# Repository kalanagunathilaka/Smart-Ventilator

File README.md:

# Smart Ventilator

This project aims to develop a low cost smart ventilator system that requires minimum professional interaction to operate using Atmega32 Microcontroller

**Objectives**

- To detect patient’s blood oxygen levels using the blood oxygen sensor (MAX30102)  and to provide oxygen where necessary.
- To monitor the patient’s vitals using the temperature sensor, pressure sensor, heart rate sensor and LCD display and send an alert message to a medical personnel using the gsm module or sound the speaker when it is necessary.
- To monitor a patient's blood oxygen level and automatically switch off oxygen supply when not needed.
- To be able to manually control all parameters of the air and oxygen flow supplied to the patient.

**System Block Diagram**

**Schematic of the product**

**3D Design of the System**

**PCB & 3D View of the Main Board**

**PCB & 3D View of the Heart Rate & SPO2**

**PCB & 3D View of Body Temperature Sensor**

**PCB & 3D View of Power Supply**

[**3D Animation**](https://dms.uom.lk/s/HgEqCMnCMRMiKYt)

**Software Used**

- Microchip Studio - Program Microcontroller
- Proteus Design Suite - Design Schematic Diagram
- KiCad EDA - Design PCB
- Blender - Design 3D View
- Adobe After Effects & Premiere Pro - Design 3D Animation

**Contributors**

- [Yesitha Sathsara](https://github.com/yesitha)
- [Shakila Kularathna](https://github.com/shakila2030)
- [Nelaka Gunawardhana](https://github.com/NelakaGunawardhana)
- [Kalana Gunathilaka](https://github.com/KalanaLakshan)
- [Piyumanthi Nisansala](https://github.com/Piyumanthi)

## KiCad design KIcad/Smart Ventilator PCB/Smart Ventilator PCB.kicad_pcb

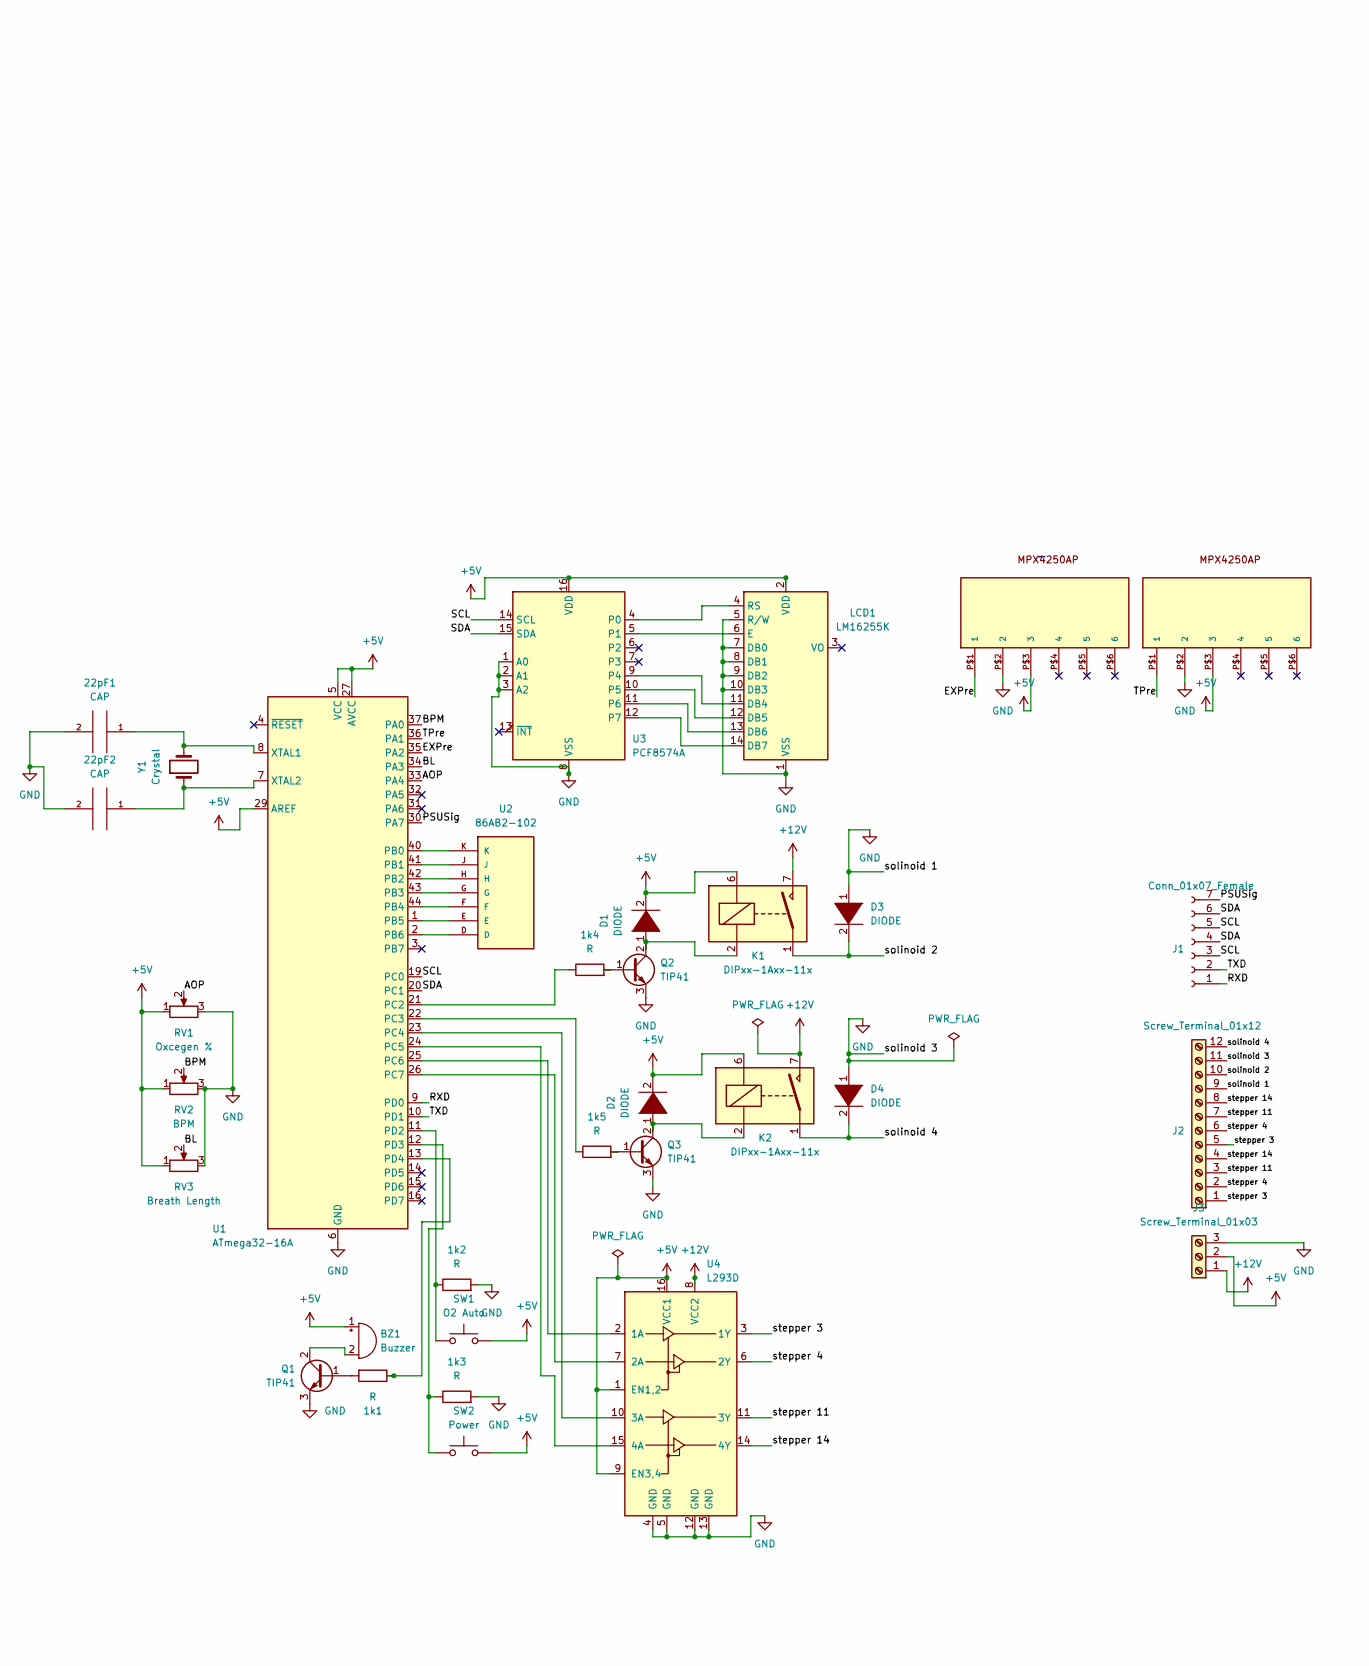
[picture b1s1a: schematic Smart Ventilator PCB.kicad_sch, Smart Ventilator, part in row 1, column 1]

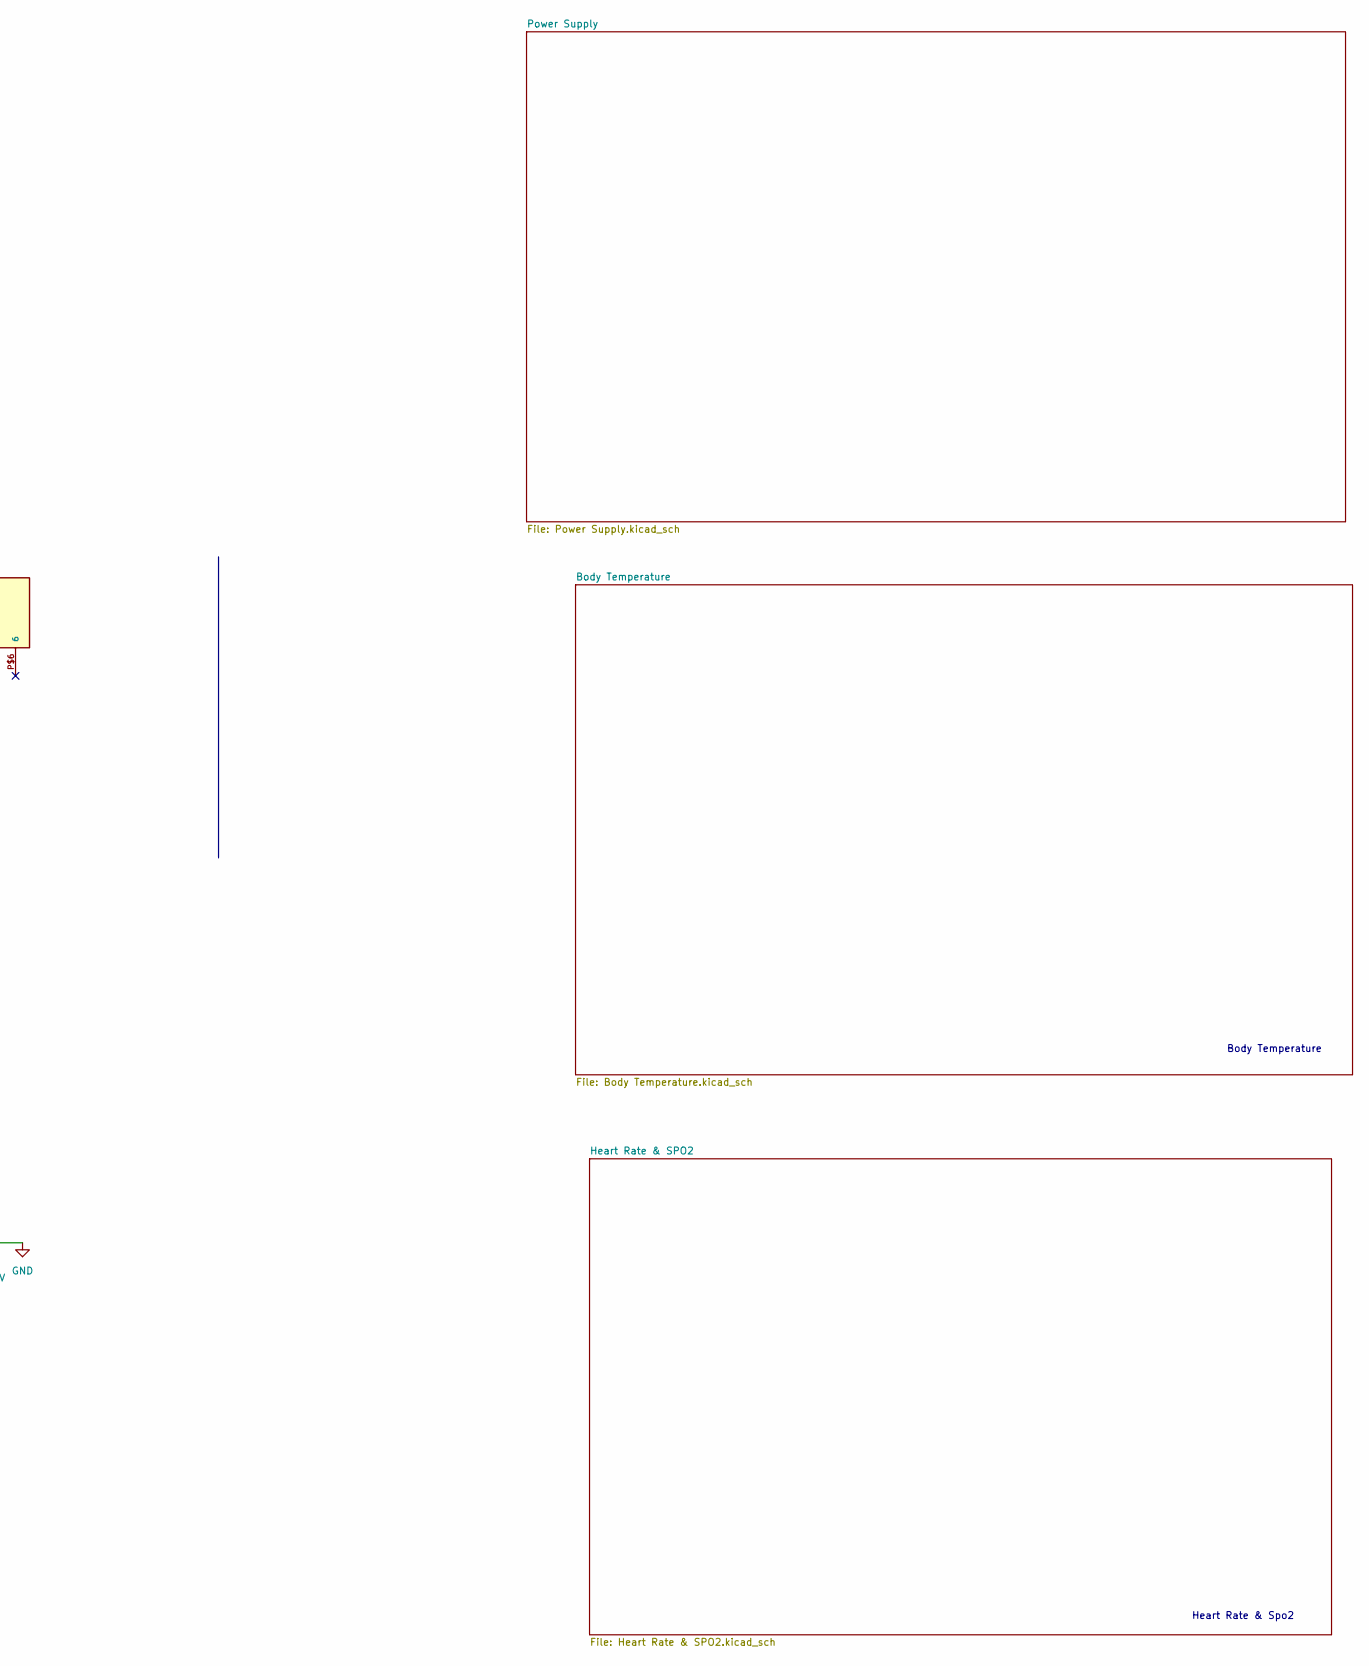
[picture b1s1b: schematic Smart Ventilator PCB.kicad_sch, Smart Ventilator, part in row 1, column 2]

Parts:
1k1, 1k2, 1k3, 1k4, 1k5: R; R_Axial_DIN0207_L6.3mm_D2.5mm_P10.16mm_Horizontal
22pF1, 22pF2: CAP; CP_Elec_3x5.3
BZ1: Buzzer; Buzzer_15x7.5RM7.6
D1, D2, D3, D4: DIODE; D_0201_0603Metric
J1: Conn_01x07_Female; PinHeader_1x07_P1.00mm_Vertical
J2: Screw_Terminal_01x12; TerminalBlock_4Ucon_1x12_P3.50mm_Horizontal
J3: Screw_Terminal_01x03; TerminalBlock_4Ucon_1x03_P3.50mm_Horizontal
K1, K2: DIPxx-1Axx-11x; Relay_StandexMeder_DIP_LowProfile
LCD1: LM16255K; LM16255
Q1, Q2, Q3: TIP41; TO-220-3_Vertical
RV1: Oxcegen %; Potentiometer_Bourns_3269W_Vertical
RV2: BPM; Potentiometer_Bourns_3269W_Vertical
RV3: Breath Length; Potentiometer_Bourns_3269W_Vertical
SW1: O2 Auto; SW_Push_1P1T_NO_6x6mm_H9.5mm
SW2: Power; SW_Push_1P1T_NO_6x6mm_H9.5mm
U1: ATmega32-16A; TQFP-44_10x10mm_P0.8mm
U2: 86AB2-102; KEYPAD_86AB2-102
U3: PCF8574A; DIL16
U4: L293D; DIP-16_W7.62mm
U5, U6: MPX4250AP
Y1: Crystal; Crystal_AT310_D3.0mm_L10.0mm_Horizontal

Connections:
+5V: BZ1.1 (-), D1.2 (A), D2.2 (A), J3.2, K1.6, K2.6, LCD1.2 (VDD), RV1.1, RV2.1, RV3.1, SW1.2, SW2.2, U1.5 (VCC), U1.17 (VCC), U1.27 (AVCC), U1.29 (AREF), U1.38 (VCC), U3.16 (VDD), U4.1 (EN1,2), U4.9 (EN3,4), U4.16 (VCC1), U5.P$3 (3), U6.P$3 (3)
+12V: J3.1, K1.7, K1.8, K2.7, K2.8, U4.8 (VCC2)
/AOP: RV1.2, U1.33 (PA4)
/BL: RV3.2, U1.34 (PA3)
/BPM: RV2.2, U1.37 (PA0)
/EXPre: U1.35 (PA2), U5.P$1 (1)
/PSUSig: J1.7, U1.30 (PA7)
/RXD: J1.1, U1.9 (PD0)
/SCL: J1.3, J1.5, U1.19 (PC0), U3.14 (SCL)
/SDA: J1.4, J1.6, U1.20 (PC1), U3.15 (SDA)
/TPre: U1.36 (PA1), U6.P$1 (1)
/TXD: J1.2, U1.10 (PD1)
/solinoid 2: D3.2 (A), J2.10, K1.1, K1.14
/solinoid 4: D4.2 (A), J2.12, K2.1, K2.14
/stepper 3: J2.1, J2.5, U4.3 (1Y)
/stepper 4: J2.2, J2.6, U4.6 (2Y)
/stepper 11: J2.3, J2.7, U4.11 (3Y)
/stepper 14: J2.4, J2.8, U4.14 (4Y)
GND: 1k2.2, 1k3.2, 22pF1.2, 22pF2.2, D3.1 (K), D4.1 (K), J2.9, J2.11, J3.3, K2.9, K2.13, LCD1.1 (VSS), LCD1.5 (R/W), LCD1.7 (DB0), LCD1.8 (DB1), LCD1.9 (DB2), LCD1.10 (DB3), Q1.3 (E), Q2.3 (E), Q3.3 (E), RV1.3, RV2.3, RV3.3, U1.6 (GND), U1.18 (GND), U1.28 (GND), U1.39 (GND), U3.1 (A0), U3.2 (A1), U3.3 (A2), U3.8 (VSS), U4.4 (GND), U4.5 (GND), U4.12 (GND), U4.13 (GND), U5.P$2 (2), U6.P$2 (2)
unnamed: 1k1.1, U1.13 (PD4)
unnamed: 1k1.2, Q1.1 (B)
unnamed: 1k2.1, SW1.1, U1.11 (PD2)
unnamed: 1k3.1, SW2.1, U1.12 (PD3)
unnamed: 1k4.1, U1.21 (PC2)
unnamed: 1k4.2, Q2.1 (B)
unnamed: 1k5.1, U1.22 (PC3)
unnamed: 1k5.2, Q3.1 (B)
unnamed: 22pF1.1, U1.8 (XTAL1), Y1.2
unnamed: 22pF2.1, U1.7 (XTAL2), Y1.1
unnamed: BZ1.2 (+), Q1.2 (C)
unnamed: D1.1 (K), K1.2, Q2.2 (C)
unnamed: D2.1 (K), K2.2, Q3.2 (C)
unnamed: LCD1.4 (RS), U3.4 (P0)
unnamed: LCD1.6 (E), U3.5 (P1)
unnamed: LCD1.11 (DB4), U3.9 (P4)
unnamed: LCD1.12 (DB5), U3.10 (P5)
unnamed: LCD1.13 (DB6), U3.11 (P6)
unnamed: LCD1.14 (DB7), U3.12 (P7)
unnamed: U1.1 (PB5), U2.E
unnamed: U1.2 (PB6), U2.D
unnamed: U1.23 (PC4), U4.10 (3A)
unnamed: U1.24 (PC5), U4.15 (4A)
unnamed: U1.25 (PC6), U4.2 (1A)
unnamed: U1.26 (PC7), U4.7 (2A)
unnamed: U1.40 (PB0), U2.K
unnamed: U1.41 (PB1), U2.J
unnamed: U1.42 (PB2), U2.H
unnamed: U1.43 (PB3), U2.G
unnamed: U1.44 (PB4), U2.F

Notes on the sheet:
Body Temperature
Heart Rate & Spo2

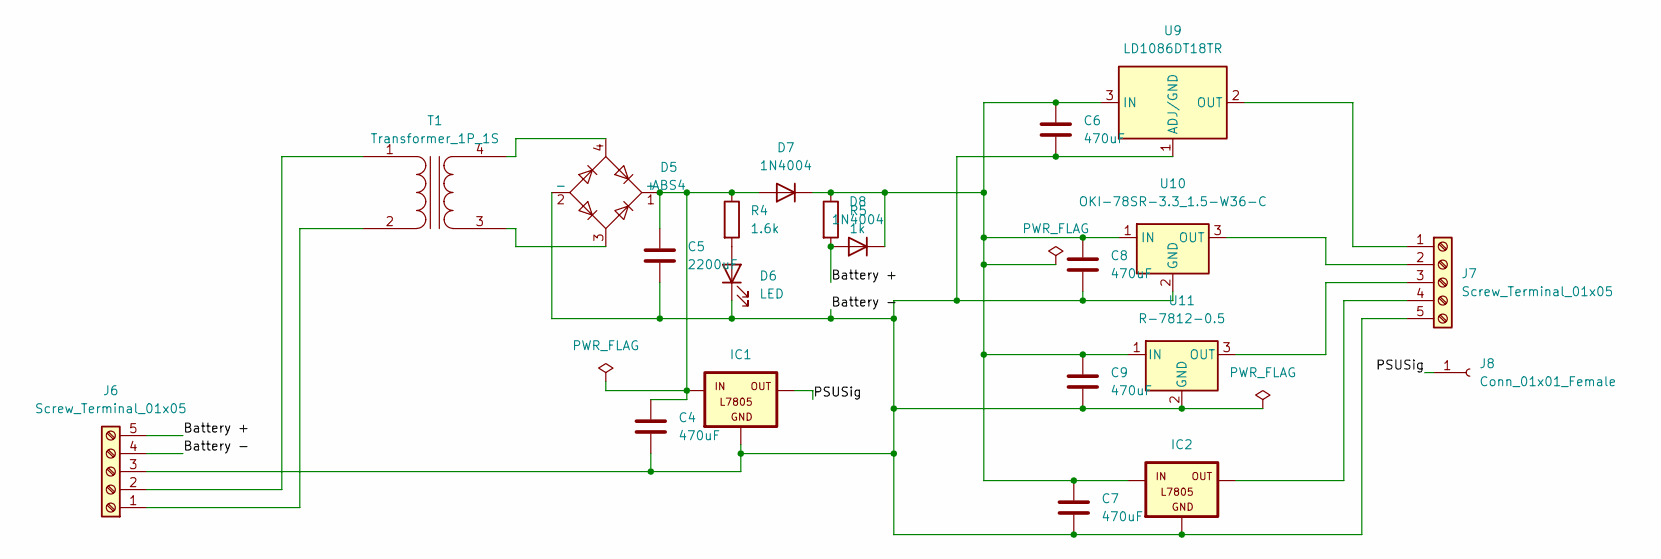
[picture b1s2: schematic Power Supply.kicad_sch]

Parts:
C4, C6, C7, C8, C9: 470uF; C_Elec_3x5.4
C5: 2200uF; C_Elec_5x5.4
D5: ABS4; Diode_Bridge_Diotec_ABS
D6: LED; LED_0603_1608Metric_Pad1.05x0.95mm_HandSolder
D7, D8: 1N4004; D_DO-41_SOD81_P10.16mm_Horizontal
IC1, IC2: L7805; 78XXL
J6, J7: Screw_Terminal_01x05; TerminalBlock_4Ucon_1x05_P3.50mm_Horizontal
J8: Conn_01x01_Female; PinHeader_1x01_P1.00mm_Vertical
R4: 1.6k; R_Axial_DIN0207_L6.3mm_D2.5mm_P10.16mm_Horizontal
R5: 1k; R_Axial_DIN0207_L6.3mm_D2.5mm_P10.16mm_Horizontal
T1: Transformer_1P_1S; Transformer_Toroid_Horizontal_D9.0mm_Amidon-T30
U9: LD1086DT18TR; TO-252-2
U10: OKI-78SR-3.3_1.5-W36-C; Converter_DCDC_Murata_OKI-78SR_Vertical
U11: R-7812-0.5; Converter_DCDC_RECOM_R-78E-0.5_THT

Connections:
/Power Supply/Battery +: D8.2 (A), J6.5, R5.2
/Power Supply/Battery -: C4.2, C5.2, C6.2, C7.2, C8.2, C9.2, D5.2 (-), D6.1 (K), IC1.GND, IC2.GND, J6.3, J6.4, J7.5, U9.1 (ADJ/GND), U10.2 (GND), U11.2 (GND)
/Power Supply/PSUSig: IC1.OUT, J8.1
unnamed: C4.1, C5.1, D5.1 (+), D7.2 (A), IC1.IN, R4.1
unnamed: C6.1, C7.1, C8.1, C9.1, D7.1 (K), D8.1 (K), IC2.IN, R5.1, U9.3 (IN), U10.1 (IN), U11.1 (IN)
unnamed: D5.3, T1.3 (SA)
unnamed: D5.4, T1.4 (SB)
unnamed: D6.2 (A), R4.2
unnamed: IC2.OUT, J7.4
unnamed: J6.1, T1.2 (AB)
unnamed: J6.2, T1.1 (AA)
unnamed: J7.1, U9.2 (OUT)
unnamed: J7.2, U10.3 (OUT)
unnamed: J7.3, U11.3 (OUT)

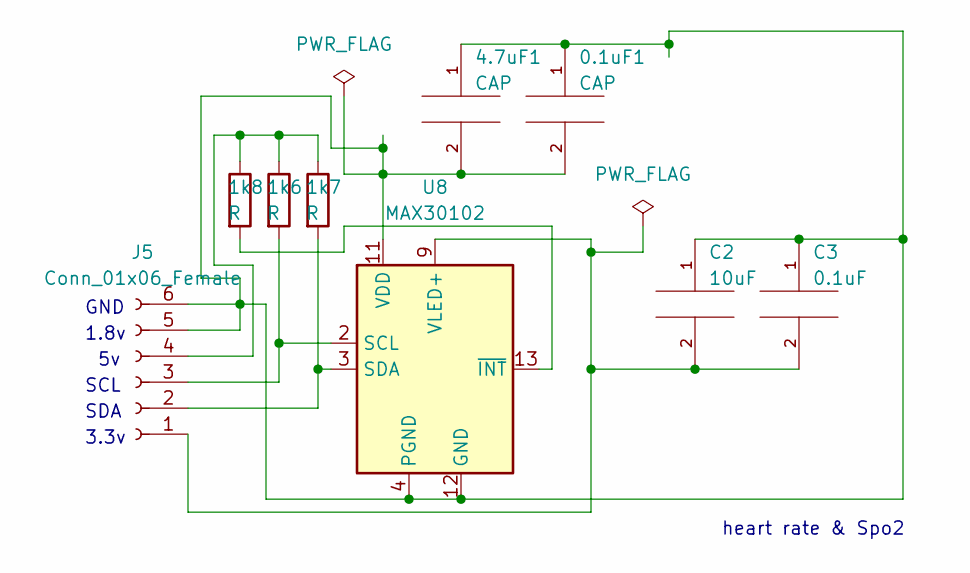
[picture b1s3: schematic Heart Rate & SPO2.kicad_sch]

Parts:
0.1uF1, 4.7uF1: CAP; CP_Elec_3x5.3
1k6, 1k7, 1k8: R; R_Axial_DIN0207_L6.3mm_D2.5mm_P10.16mm_Horizontal
C2: 10uF; CP_Elec_3x5.3
C3: 0.1uF; CP_Elec_3x5.3
J5: Conn_01x06_Female; PinHeader_1x06_P1.00mm_Vertical
U8: MAX30102; Maxim_OLGA-14_3.3x5.6mm_P0.8mm

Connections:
unnamed: 0.1uF1.1, 0.1uF1.2, 4.7uF1.1, 4.7uF1.2, C2.1, C3.1, J5.5, J5.6, U8.4 (PGND), U8.11 (VDD), U8.12 (GND)
unnamed: 1k6.1, 1k7.1, 1k8.1, J5.4
unnamed: 1k6.2, U8.13 (~INT)
unnamed: 1k7.2, J5.3, U8.2 (SCL)
unnamed: 1k8.2, J5.2, U8.3 (SDA)
unnamed: C2.2, C3.2, J5.1, U8.9 (VLED+), U8.10 (VLED+)

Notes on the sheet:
heart rate & Spo2
GND
SDA
1.8v
SCL
3.3v

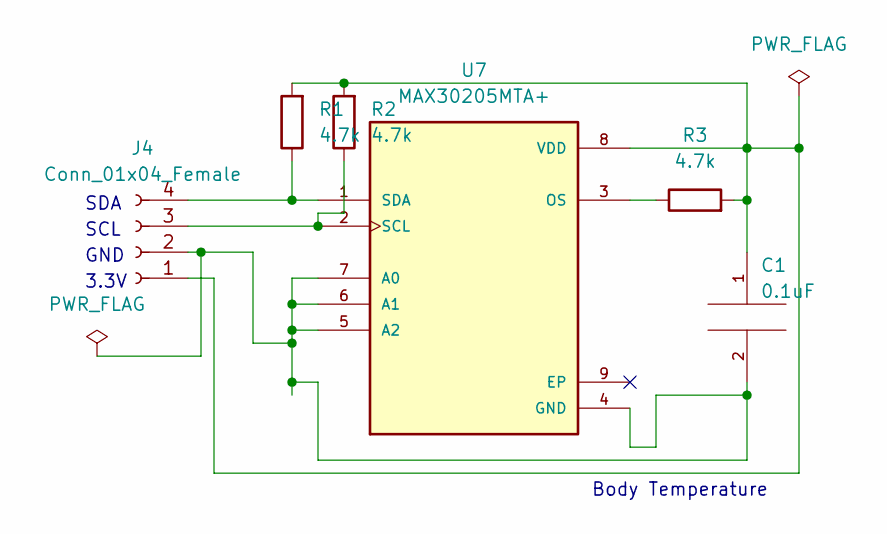
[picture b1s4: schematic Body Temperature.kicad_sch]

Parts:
C1: 0.1uF; CP_Elec_3x5.3
J4: Conn_01x04_Female; PinHeader_1x04_P1.00mm_Vertical
R1, R2, R3: 4.7k; R_Axial_DIN0207_L6.3mm_D2.5mm_P10.16mm_Horizontal
U7: MAX30205MTA+; SON65P300X300X80-9N

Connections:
unnamed: C1.1, J4.1, R1.2, R2.2, R3.2, U7.8 (VDD)
unnamed: C1.2, J4.2, U7.4 (GND), U7.5 (A2), U7.6 (A1), U7.7 (A0)
unnamed: J4.3, R2.1, U7.2 (SCL)
unnamed: J4.4, R1.1, U7.1 (SDA)
unnamed: R3.1, U7.3 (OS)

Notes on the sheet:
3.3V
SDA
SCL
Body Temperature
GND

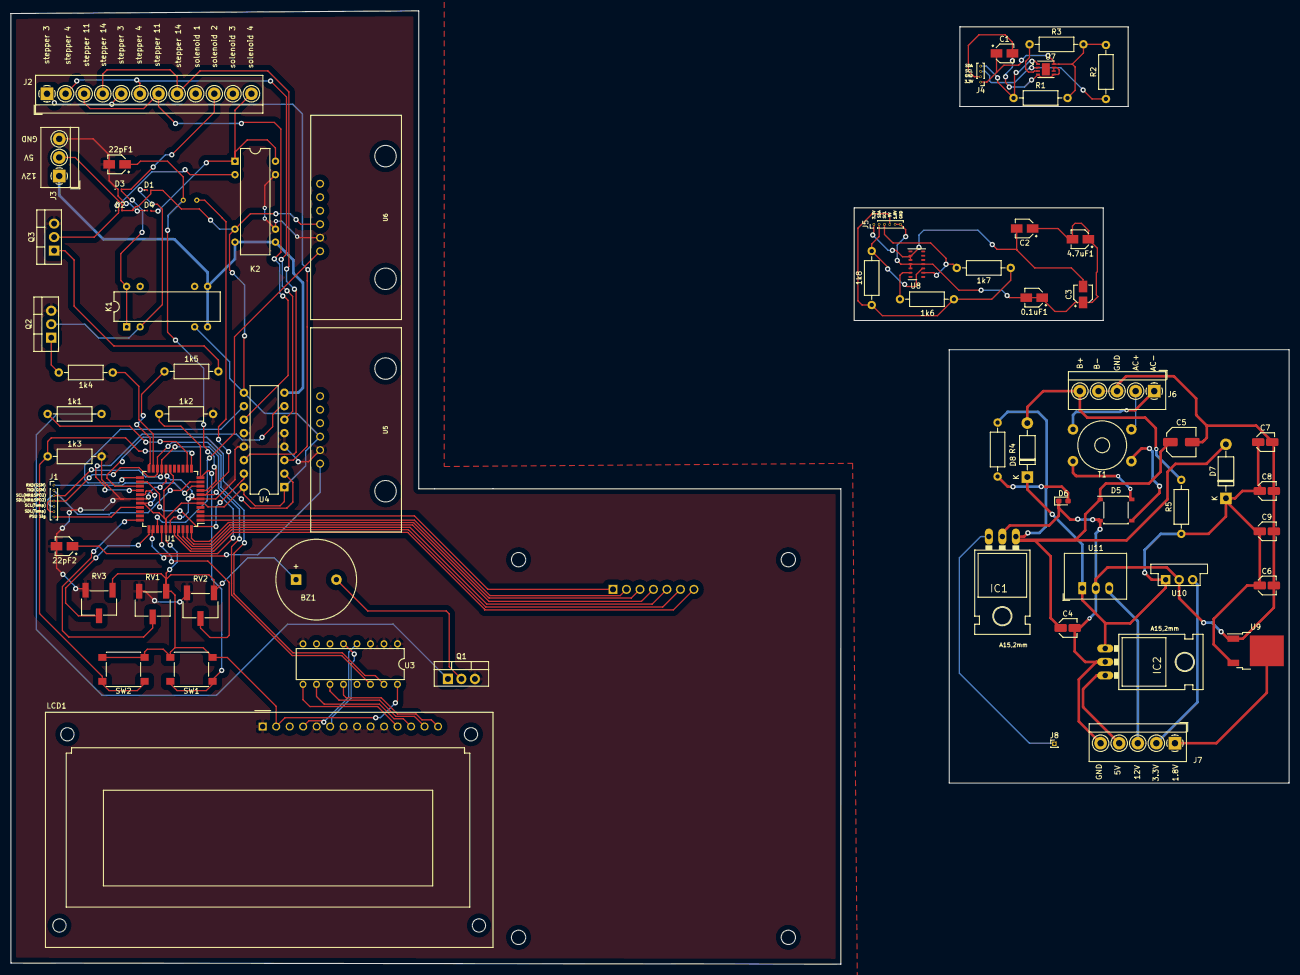
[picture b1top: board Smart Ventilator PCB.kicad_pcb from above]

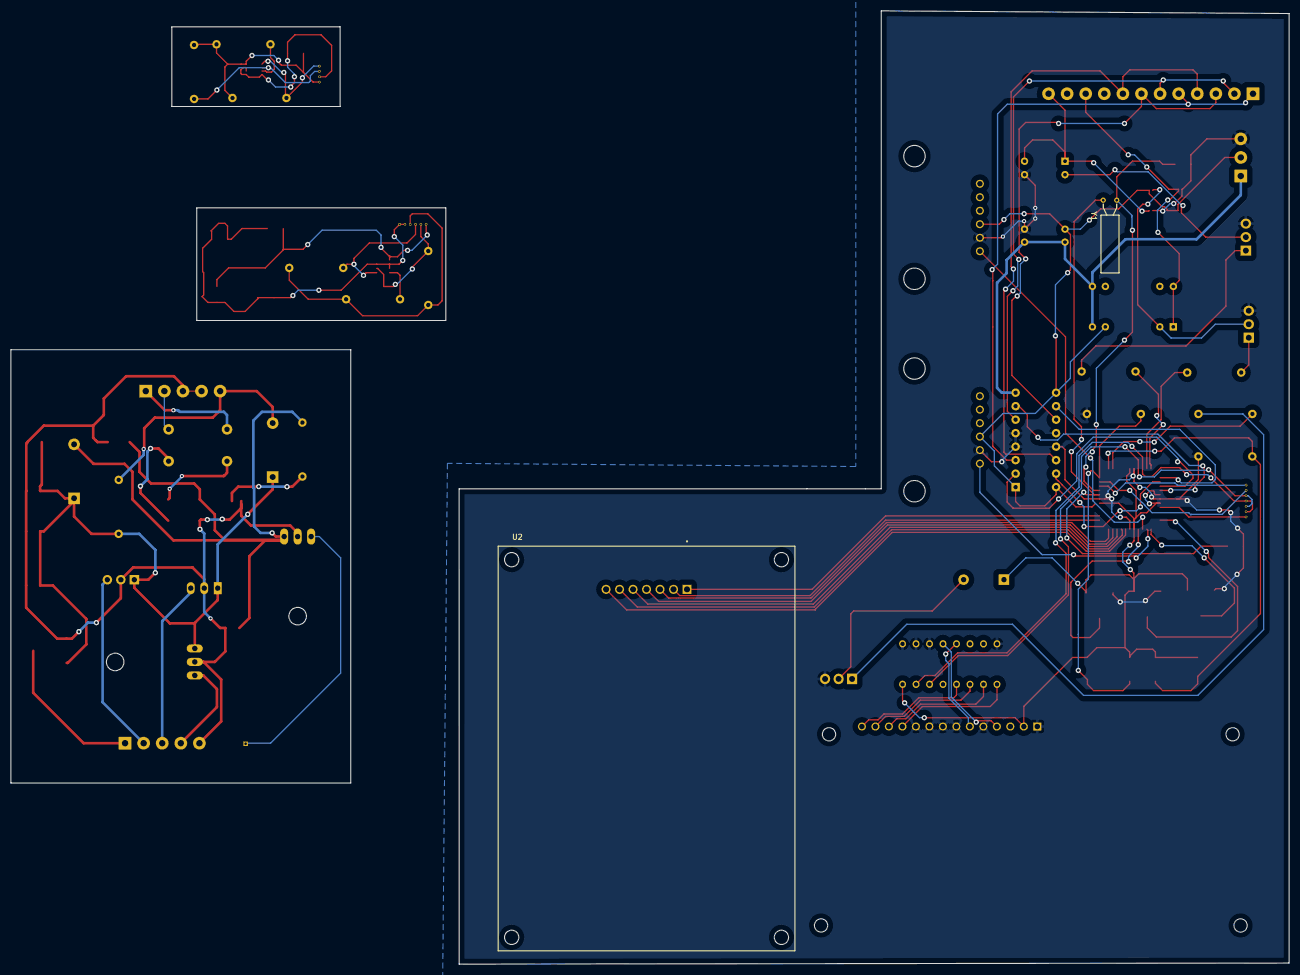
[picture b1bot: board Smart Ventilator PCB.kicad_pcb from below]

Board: 2 copper layers, 240.7 x 179.5 mm, 69 parts (2 on the bottom side), 74 nets.

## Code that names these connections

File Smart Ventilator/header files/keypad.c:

/*
 * GccApplication2.c
 *
 * Created: 5/12/2022 11:27:58 PM
 * Author : Piyumanthi
 */ 
#define F_CPU 16000000UL
#include <avr/io.h>
#include<util/delay.h>
#include "LCD16x2_4bit.h"

char Keypad()
{
	
	PORTB=0b1111110;         // make first row 0
	if((PINB &(1<<PINB4))==0)
	{
		_delay_ms(3);
		return'1';
	}

	else if((PINB&(1<<PINB5))==0)
	{
		_delay_ms(3);
		return'2';
	}
	else if((PINB&(1<<PINB6))==0)
	{
		_delay_ms(3);
		return'3';
	}
	

	PORTB=0b1111101;   // make second row 0
	if((PINB &(1<<PINB4))==0)
	{
		_delay_ms(3);
		return'4';
	}
	else if((PINB&(1<<PINB5))==0)
	{
		_delay_ms(3);
		return'5';
	}
	else if((PINB&(1<<PINB6))==0)
	{
		_delay_ms(3);
		return'6';
	}
	

	PORTB=0b1111011;   // make third row 0
	if((PINB &(1<<PINB4))==0)
	{
		_delay_ms(3);
		return'7';
	}
	else if((PINB&(1<<PINB5))==0)
	{
		_delay_ms(3);
		return'8';
	}
	else if((PINB&(1<<PINB6))==0)
	{
		_delay_ms(3);
		return'9';
	}
	

	PORTB=0b1110111;   // make fourth row 0
	if((PINB &(1<<PINB4))==0)
	{
		_delay_ms(3);
		return'*';
	}
	else if((PINB&(1<<PINB5))==0)
	{
		_delay_ms(3);
		return'0';
	}
	else if((PINB&(1<<PINB6))==0)
	{
		_delay_ms(3);
		return'#';
	}
	

}

int main(void)
{
	unsigned char x;
	DDRB=0x0F;         //Make PB0 to PB3 = output and PB4 to PB6=input
	LCD_Init ();
	while(1)
	{
		PORTB =0xF0;   //Make all columns 1 and all rows 0.
		if(PINB!=0xF0)
		{
			x=Keypad();
			LCD_Char(x);
		}
		
	}
	return 0;
}

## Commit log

2021-11-27 Changes in main.c
2021-12-03 update solenoid valve control
2021-12-05 update solenoid valve open
2021-12-09 Notify GSM Added
2022-04-24 Update Notify GSM
2022-05-11 Update GSM Module
2022-05-12 change isp
2022-05-13 Update solenoid valve
2022-05-14 update stepper motor
2022-05-15 stepper motor header added
2022-05-15 Display Header Added
2022-05-15 Proteus Project Added
2022-05-15 Timer Delay Added
2022-05-15 solenoid valve and stepper motor work simultaneously
2022-05-16 keypad updated
2022-05-16 External Interrupt Added
2022-05-17 Potentiometer meter Added
2022-05-17 Speaker, Potentiometer Added.
2022-05-19 changed keypad code
2022-05-22 buttons added
2022-05-22 parameters changed
2022-05-23 Potentiometer logic Updated
2022-05-23 Power Supply Added
2022-05-24 changes to lcd-enter no
2022-05-24 Display Information's Delay Updated
2022-05-24 update display information
2022-05-24 Add Pressure and Temperature Sensor
2022-05-24 Change Pressure value
2022-05-24 lcd gsm array success
2022-05-24 display additions
2022-06-07 GSM Code Updated
2022-06-08 PCB Added
2022-06-08 Proteus file updated
2022-07-01 readMe files Added
